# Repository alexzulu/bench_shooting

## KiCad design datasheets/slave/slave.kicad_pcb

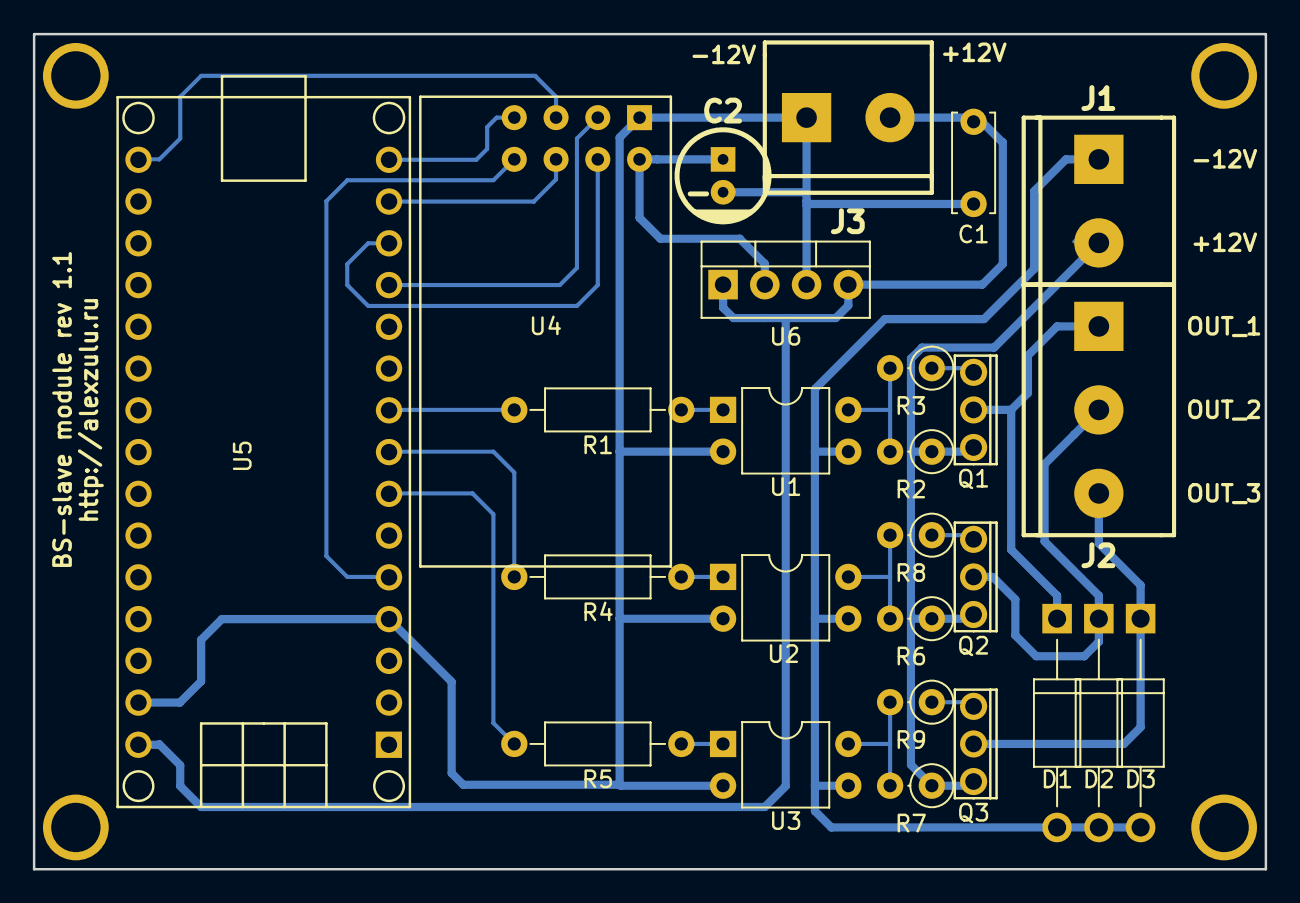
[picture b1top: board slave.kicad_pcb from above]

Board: 2 copper layers, 74.9 x 50.8 mm, 26 parts (0 on the bottom side), 26 nets.

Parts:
C1: C; C_Disc_D6.0mm_W2.5mm_P5.00mm
C2: CP; CP_5x11mm
D1, D2, D3: 1N4007; D_DO-41_SOD81_P12.70mm_Horizontal
J1, J3: Screw_Terminal_1x02; mors_2p
J2: Screw_Terminal_1x03; mors_3p
Q1, Q2, Q3: IRFU9024N; TO-251AA
R1: 470; R_Axial_DIN0207_L6.3mm_D2.5mm_P10.16mm_Horizontal
R2: 10k; R_Axial_DIN0207_L6.3mm_D2.5mm_P2.54mm_Vertical
R3: 100; R_Axial_DIN0207_L6.3mm_D2.5mm_P2.54mm_Vertical
R4, R5: R; R_Axial_DIN0207_L6.3mm_D2.5mm_P10.16mm_Horizontal
R6, R7, R8, R9: R; R_Axial_DIN0207_L6.3mm_D2.5mm_P2.54mm_Vertical
U1, U2, U3: PC817; DIP-4_W7.62mm
U4: nRF24L01; nRF24L01-NA
U5: ArduinoNano
U6: KA378R33; TO-220-4_Vertical

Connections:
/3V3: C2.1, U4.2, U6.2
/CE/SS: U4.3, U5.12
/D_GND: C1.2, C2.2, J3.1, U1.2, U2.2, U3.2, U4.1, U5.4, U5.29, U6.3
/D_VCC: C1.1, J3.2, U5.30, U6.1, U6.4
/IN_1: R1.2, U5.9
/IN_2: R4.2, U5.8
/IN_3: R5.2, U5.7
/IRQ: U4.8, U5.5
/MISO: U4.7, U5.15
/MOSI: U4.6, U5.14
/OUT_1: D1.1, J2.1, Q1.2
/OUT_2: D2.1, J2.2, Q2.2
/OUT_3: D3.1, J2.3, Q3.2
/P_GND: D1.2, D2.2, D3.2, J1.1, U1.3, U2.3, U3.3
/P_VCC: J1.2, Q1.3, Q2.3, Q3.3, R2.1, R6.1, R7.1
/SCK: U4.5, U5.16
/SCN: U4.4, U5.13
unnamed: Q1.1, R3.1
unnamed: Q2.1, R8.1
unnamed: Q3.1, R9.1
unnamed: R1.1, U1.1
unnamed: R2.2, R3.2, U1.4
unnamed: R4.1, U2.1
unnamed: R5.1, U3.1
unnamed: R6.2, R8.2, U2.4
unnamed: R7.2, R9.2, U3.4

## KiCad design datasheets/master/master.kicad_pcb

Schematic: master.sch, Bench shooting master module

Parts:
J1, J2, J3, J4, J5: Screw_Terminal_01x03; mors_3p
J6: Screw_Terminal_01x02; mors_2p
U1: nRF24L01+PA; nRF24L01-NA
U2: ArduinoNano

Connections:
+3V3: U1.2 (VCC)
+5V: J1.3, J2.3, J3.3, J4.3, J5.3, U2.27 (5V)
+12V: J6.1, U2.30 (VIN)
/A0: J1.1, U2.19 (A0)
/A1: J2.1, U2.20 (A1)
/A2: J3.1, U2.21 (A2)
/A3: J4.1, U2.22 (A3)
/A4: J5.1, U2.23 (A4)
/CE/SS: U1.3 (CE), U2.12 (D9)
/IRQ: U1.8 (IRQ)
/MISO: U1.7 (MISO), U2.15 (D12)
/MOSI: U1.6 (MOSI), U2.14 (D11)
/SCK: U1.5 (SCK), U2.16 (D13)
/SCN: U1.4 (CSN), U2.13 (D10)
GND: J1.2, J2.2, J3.2, J4.2, J5.2, J6.2, U1.1 (GND), U2.4 (GND), U2.29 (GND)

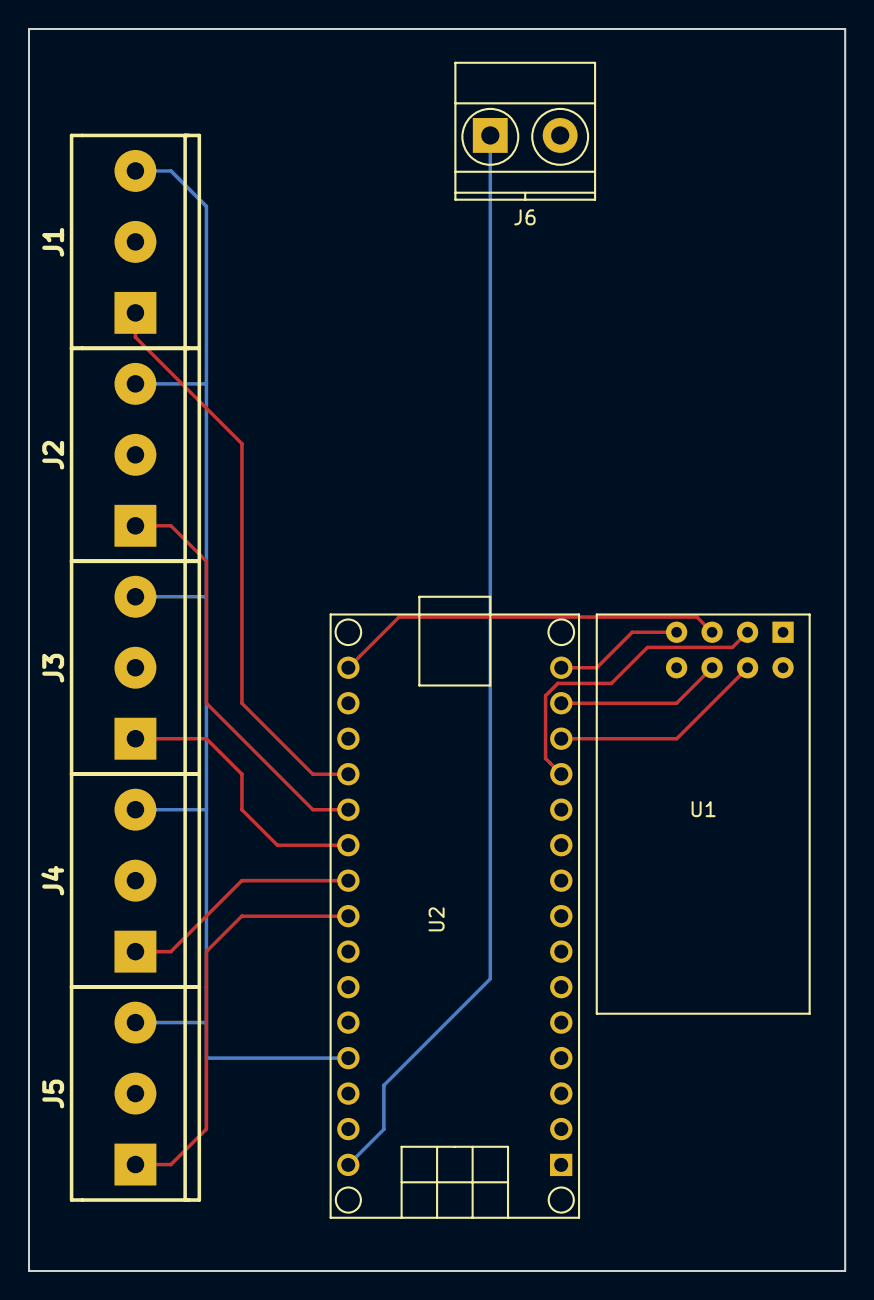
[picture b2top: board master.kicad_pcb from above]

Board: 2 copper layers, 58.4 x 88.9 mm, 8 parts (0 on the bottom side), 13 nets.

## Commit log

2017-07-11 Разработка схемы силового модуля
2017-07-30 Начал описывать логику. Нарисовал часть схемы управления.
2017-08-03 Правка логики. Правка схемы для симуляции.
2017-09-05 Перешёл на KICad. Схемы и платы в нём.
2017-09-11 Исправление ошибок в схемах
2017-09-21 Правка схем
2017-10-27 Добавление библиотек компонентов для KiCad.
2017-10-27 Проблема с бибилиотеками KiCad
2017-10-27 Теперь файлы *.lib не игнорируются.
2017-10-27 Удаление лишнего. Попытка синхронизации Lin/Win.
2017-10-27 Обновление библиотек KiCad
2017-10-27 Добавил 3D модели
2017-12-20 Исправление ошибок. Неправильные MOSI и MISO
2017-12-21 Правка схем. Наведение красивости.
2017-12-22 Синхронизация библиотек. Новый модуль.
2017-12-23 Добавление документации по электронным компонентам
2018-07-05 Разделение системы управления на master и master_light
2018-07-05 Обновление и добавление документации.
